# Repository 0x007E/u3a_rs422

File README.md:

# `U3A_rs422` - RS422 - Adapter for U3A

The `U3A_rs422` project is based on a ([THVD1452](#additional-information)) that ist used to change the RX/TX signals to the required differential signal level of TIA/TIA-485-A standard. It can simply be adapted to the [U3A-Module](https://github.com/0x007e/u3a).

> To use it with a [DSUB](https://www.reichelt.de/de/de/shop/produkt/d-sub-stecker_9-pol_flachbandkabel_ohne_isolator-6987) connector it is necessary to create a connector cable that can be plugged into the IDC connector.

| Experience | Level |
|:------------|:-----:|
| Soldering   |  |
| Mechanical  |  |

# Downloads

| Type       | File               | Description              |
|:----------:|:------------------:|:-------------------------|
| Schematic  | [pdf](https://github.com/0x007E/u3a_rs422/releases/latest/download/schematic.pdf) / [cadlab](https://cadlab.io/project/29767/main/files) | Schematic files |
| Board      | [pdf](https://github.com/0x007E/u3a_rs422/releases/latest/download/pcb.pdf) / [cadlab](https://cadlab.io/project/29767/main/files) | Board file |
| Drill      | [pdf](https://github.com/0x007E/u3a_rs422/releases/latest/download/drill.pdf) | Drill file |
| BoM | [xlsx](https://github.com/0x007E/u3a_rs422/releases/latest/download/bom.xlsx) / [html](https://github.com/0x007E/u3a_rs422/releases/latest/download/ibom.html)          | Bill of Material as Excel/interactive HTML |
| PCB    | [zip](https://github.com/0x007E/u3a_rs422/releases/latest/download/kicad.zip) / [tar](https://github.com/0x007E/u3a_rs422/releases/latest/download/kicad.tar.gz)    | KiCAD/Gerber/BoM/Drill files       |
| Mechanical | [zip](https://github.com/0x007E/u3a_rs422/releases/latest/download/freecad.zip) / [tar](https://github.com/0x007E/u3a_rs422/releases/latest/download/freecad.tar.gz) | FreeCAD/Housing and PCB (STEP/STL) files     |

# Hardware

There are two parts of the hardware. The pcb and the housing of the `U3A_rs422`. The pcb is created with [KiCAD](#additional-information) and the housing with [FreeCAD](#additional-information). All files are built with `github actions` so that they are ready for a production environment. The housing is printed with a 3D-printer (`Dremel 3D40`).

## PCB

The circuit board is populated on both sides (Top, Bottom). The best way for soldering the `SMD` components is within a vapor phase soldering system and for the `THT` components with a standard soldering system.

### Top Layer

### Bottom Layer

## Mechanical

The housing has a tolerance of `0.2mm` on each side of the case. So the pcb should fit perfectly in the housing. The tolerance can be modified with `FreeCAD` in the `Parameter` Spreadsheet.

### Assembled

### Exploded

# Connection/Setup

The `U3A_rs422` is powerd over the `U3A` board with `5V`. The voltage of the pins are driven by a `THVD1452` for data transmission that meets the TIA/TIA-485-A standard.

## Simple loopback setup for testing purpose

``` bash
#
#            +------------------------------------+           +-----------------------------------+      +---------------------+
#            |J1                      T         J2|           |J2     U                       +---+---+  |                     |
#         +--+--+        U3A_rs422    E        +--+--+     +--+--+    S                U      |  USB  |--+ +-----------------+ |
#     +---+ RTS-| (1) D               R        | VCC +-----+ VCC |    B      UPDI      3      +---+---+  | | TeraTerm        | |
#   L | +-+ RTS+| (2) B               M        | GND +-----+ GND |    /    +---+---+   A          |      | | ~~~~~~~~        | |
#   O +-|-+ CTS-| (3) 9               I        |  X  +-----| PDI |    U    |   |   |              |      | | ~~~~~           | |
#   O   +-+ CTS+| (4)                 N        | CTS +-----+ CTS |    A    |   |   |              |      | | ~~~~~~~~~~~~    | |
#   P     + GND | (5)                 A        | RTS +-----+ RTS |    R    | X | X |              |      | |                 | |
#   B   +-+ RXD+| (6) ~               T        | TXD +-----+ TXD |    T    +---+---+     +-+      |      | +-----------------+ |
#   A +-|-+ RXD-| (7) P   T           I        | RXD +-----+ RXD |    /                 / /       |      |                     |
#   C | +-+ TXD+| (8) W   X           O        +--+--+     +--+--+    U               +-+-+-+-+-+-+      | Computer            |
#   K +---+ TXD-| (9) R   D           N           |           |       P               | 5V  | 3V3 |      |                     |
#         +--+--+     E   E           -> 120Ω     |           |       D               +-----+-----+      +---------------------+
#            |        N   N                       |           |       I         J4                |
#            |  +---+---+---+---+---+---+---+---+ |           | +---+---+---+---+---+---+---+---+ |
#            |  | V | C | C | D | D | D | R | G | |           | | V | C | C | D | D | D | R | G | |
#            +--+ C | B | B | C | T | C | I | N +-+           +-+ C | B | B | C | T | C | I | N +-+
#               | C | 3 | 2 | D | R | R |   | D |               | C | 3 | 2 | D | R | R |   | D |
#               +---+-+-+-+-+---+---+---+---+---+               +---+-+-+-+-+---+---+---+---+---+
#                     |   |                                           |   |
#                     |   +-------------------------------------------|---+
#                     +-----------------------------------------------+
```

# Additional Information

| Type       | Link                                                  | Description                                          |
|:----------:|:-----------------------------------------------------:|:-----------------------------------------------------|
| THVD1452   | [pdf](https://www.ti.com/lit/ds/symlink/thvd1452.pdf) | UART / RS422 level converter                         |
| KiCAD      | [web](https://www.kicad.org/)                         | KiCAD project page                                   |
| FreeCAD    | [web](https://www.freecad.org/)                       | FreeCAD project page                                 |

---

R. GAECHTER

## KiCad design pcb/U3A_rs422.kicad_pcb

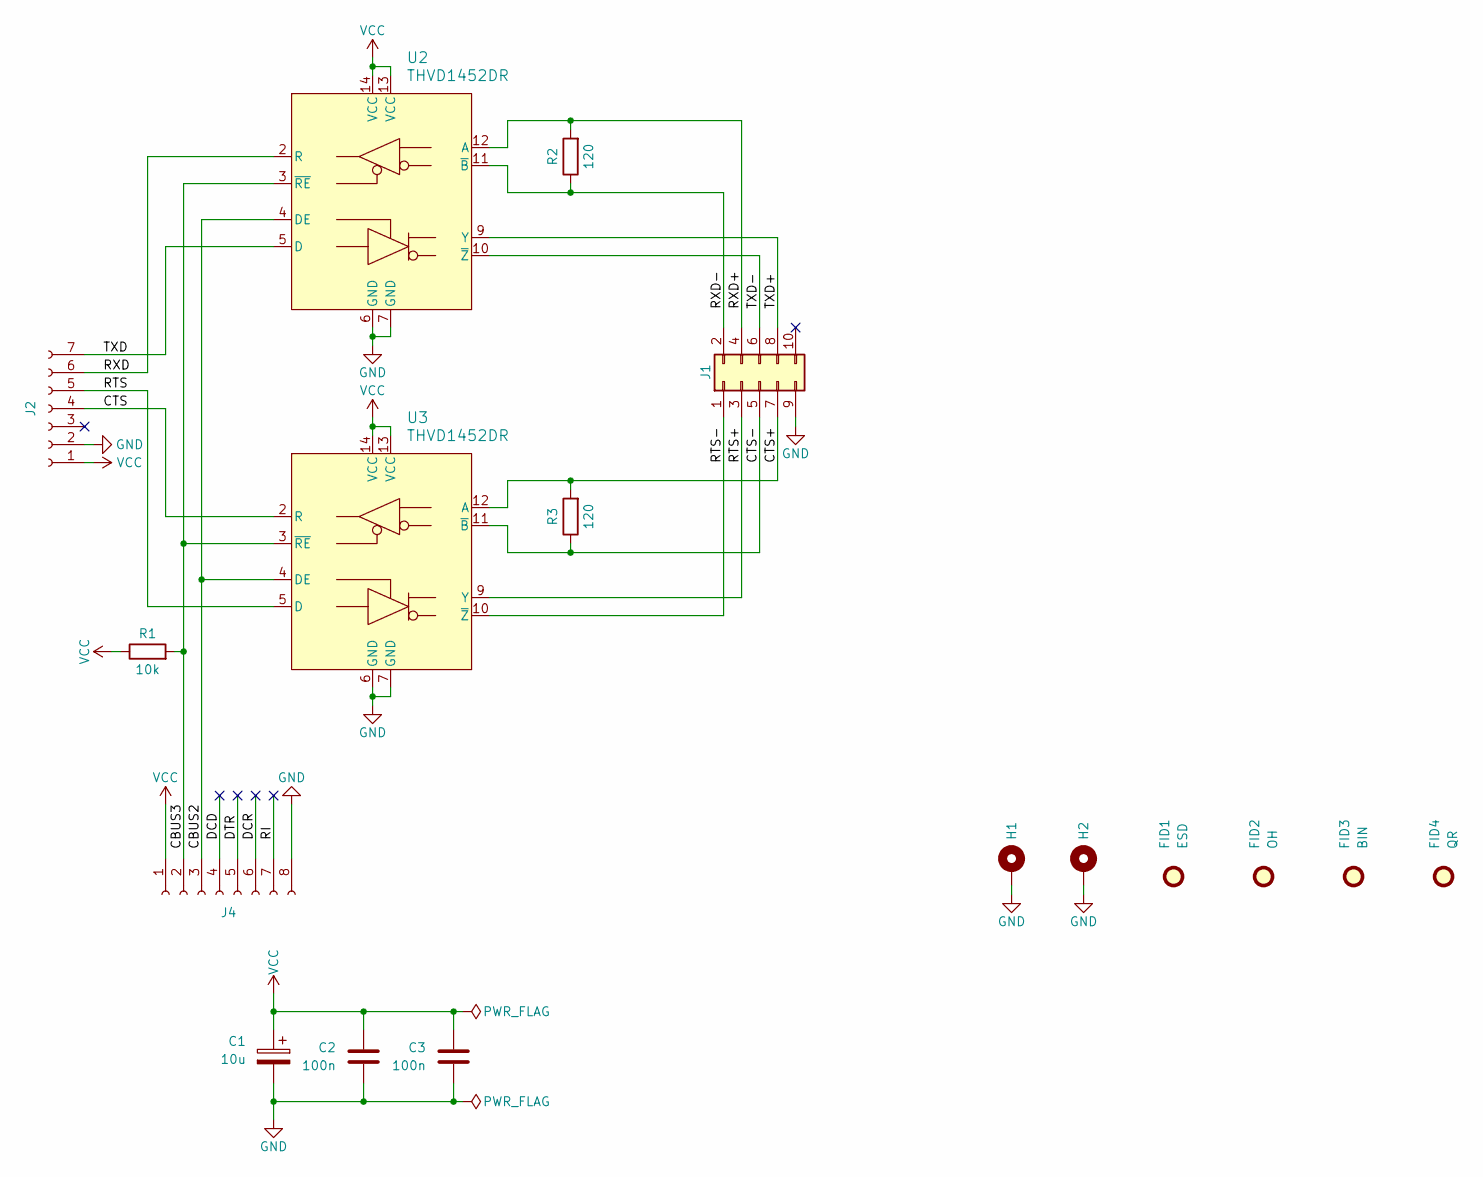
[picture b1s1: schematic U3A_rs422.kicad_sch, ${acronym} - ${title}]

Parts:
C1: 10u; CP_EIA-6032-28_Kemet-C
C2, C3: 100n; C_1206_3216Metric
FID1: ESD; ESD-Logo_6.6x6mm_SilkScreen
FID2: OH; OSHW-Logo_5.7x6mm_SilkScreen
FID3: BIN; WEEE-Logo_4.2x6mm_SilkScreen
FID4: QR; QR_0x007e_very_small
H1, H2: MountingHole_Pad; MountingHole_2.7mm_M2.5_Pad
J1: Conn_02x05_Odd_Even; IDC-Header_2x05_P2.54mm_Vertical
J2: Conn_01x07_Socket; PinSocket_1x07_P2.54mm_Vertical
J4: Conn_01x08_Socket; PinSocket_1x08_P2.54mm_Vertical
R1: 10k; R_1206_3216Metric
R2, R3: 120; R_1206_3216Metric
U2, U3: THVD1452DR; SOIC-14_3.9x8.7mm_P1.27mm

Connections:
/CBUS2: J4.3, U2.4 (DE), U3.4 (DE)
/CBUS3: J4.2, R1.2, U2.3 (~RE), U3.3 (~RE)
/CTS: J2.4, U3.2 (R)
/CTS+: J1.7, R3.2, U3.12 (A)
/CTS-: J1.5, R3.1, U3.11 (~B)
/DCD: J4.4
/DCR: J4.6
/DTR: J4.5
/RI: J4.7
/RTS: J2.5, U3.5 (D)
/RTS+: J1.3, U3.9 (Y)
/RTS-: J1.1, U3.10 (~Z)
/RXD: J2.6, U2.2 (R)
/RXD+: J1.4, R2.2, U2.12 (A)
/RXD-: J1.2, R2.1, U2.11 (~B)
/TXD: J2.7, U2.5 (D)
/TXD+: J1.8, U2.9 (Y)
/TXD-: J1.6, U2.10 (~Z)
GND: C1.2, C2.1, C3.1, H1.1, H2.1, J1.9, J2.2, J4.8, U2.6 (GND), U2.7 (GND), U3.6 (GND), U3.7 (GND)
VCC: C1.1, C2.2, C3.2, J2.1, J4.1, R1.1, U2.13 (VCC), U2.14 (VCC), U3.13 (VCC), U3.14 (VCC)

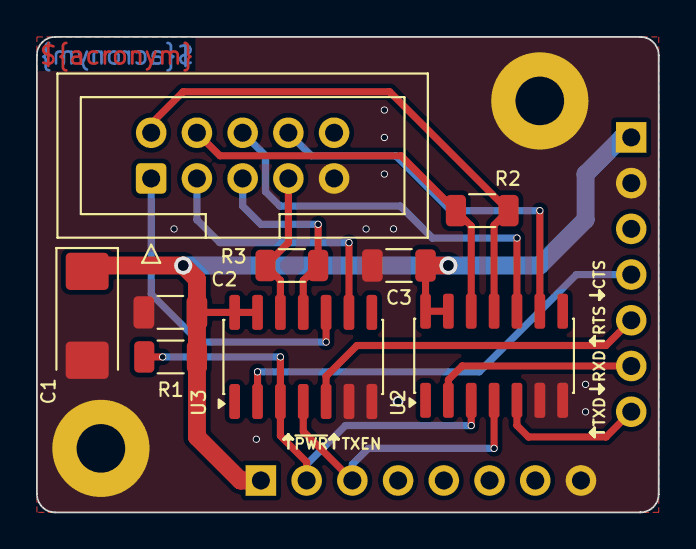
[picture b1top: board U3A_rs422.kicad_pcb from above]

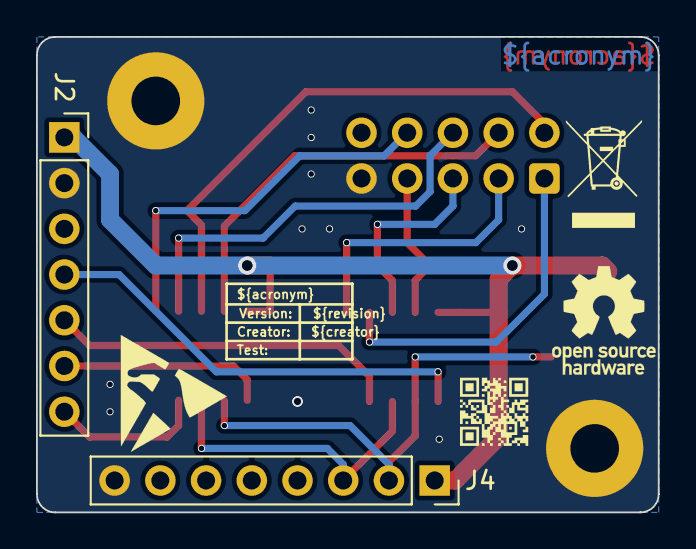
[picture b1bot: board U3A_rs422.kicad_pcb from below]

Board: 2 copper layers, 34.5 x 26.4 mm, 17 parts (6 on the bottom side), 16 nets.

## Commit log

2025-11-24 Add pcb layout
2025-11-24 Add mechanical parts
2025-11-24 Add build pipeline
2025-11-24 Add release pipeline
2025-11-24 Add README.md
2025-11-24 Replacement of pcb
2025-11-24 Image update due to circuit board replacement
2025-11-25 Add deepwiki badge
2025-11-26 Change vendor of parts
2025-12-10 Rename housing part
2026-06-19 Update to KiCAD 9
2026-06-19 Rename/Add/Remove bom fields
2026-06-19 Optimize fabrication layer
2026-06-19 Update build pipeline
2026-06-19 Update release pipeline
2026-06-19 Add thumbnail creation
2026-06-22 Adapt output filenames
2026-06-22 Add missing values in bom
2026-06-22 Adapt config and update action versions
2026-06-22 Fix freecad path issue

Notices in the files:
README.md:
License CC By-NC-SA
parts and their libraries:
license: CC BY-NC-SA 4.0
